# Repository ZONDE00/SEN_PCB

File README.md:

# SEN_PCB
Must be atleast 18 years old to clone

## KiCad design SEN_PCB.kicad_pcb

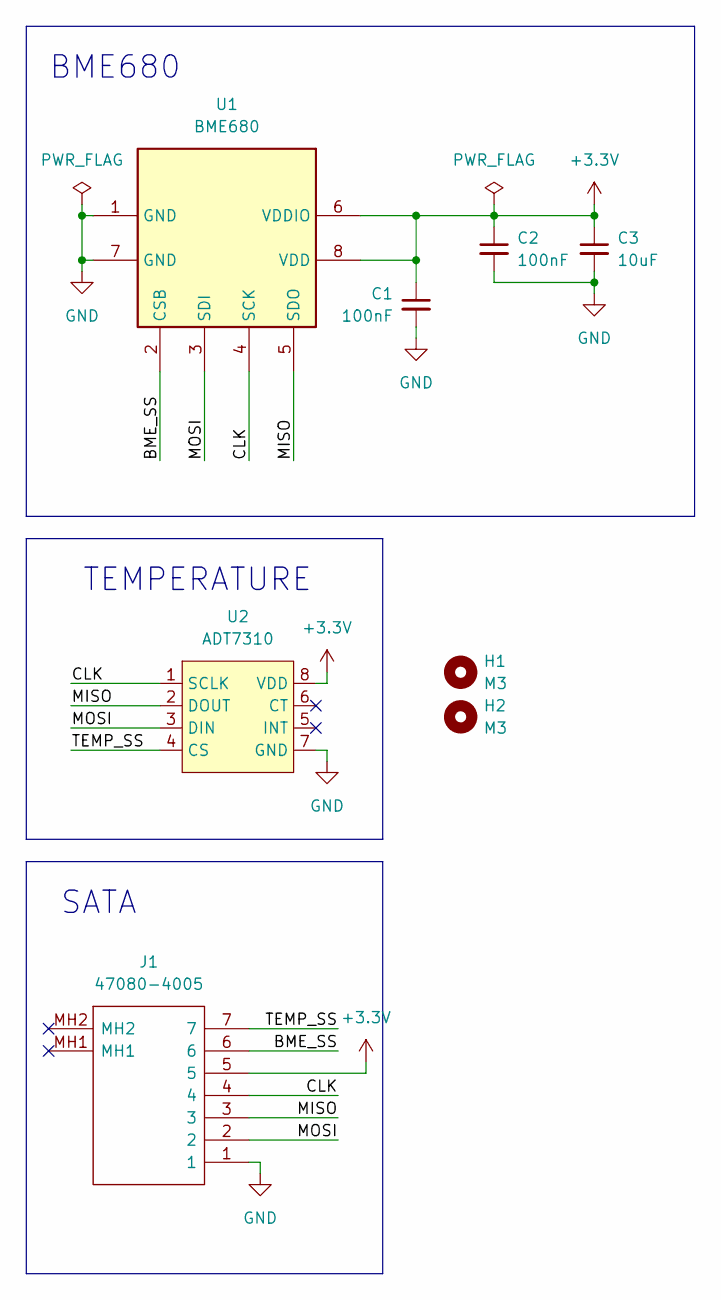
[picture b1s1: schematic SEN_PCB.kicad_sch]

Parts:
C1, C2: 100nF; C_0402_1005Metric
C3: 10uF; C_0805_2012Metric
H1, H2: M3; MountingHole_3.2mm_M3
J1: 47080-4005; 470804005; Mouser Part Number 538-47080-4005
U1: BME680; Bosch_LGA-8_3x3mm_P0.8mm_ClockwisePinNumbering
U2: ADT7310; SOIC-8_3.9x4.9mm_P1.27mm

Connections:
+3.3V: C1.1, C2.1, C3.1, J1.5, U1.6 (VDDIO), U1.8 (VDD), U2.8 (VDD)
/BME_SS: J1.6, U1.2 (CSB)
/CLK: J1.4, U1.4 (SCK), U2.1 (SCLK)
/MISO: J1.3, U1.5 (SDO), U2.2 (DOUT)
/MOSI: J1.2, U1.3 (SDI), U2.3 (DIN)
/TEMP_SS: J1.7, U2.4 (CS)
GND: C1.2, C2.2, C3.2, J1.1, U1.1 (GND), U1.7 (GND), U2.7 (GND)

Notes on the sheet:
SATA
TEMPERATURE
BME680

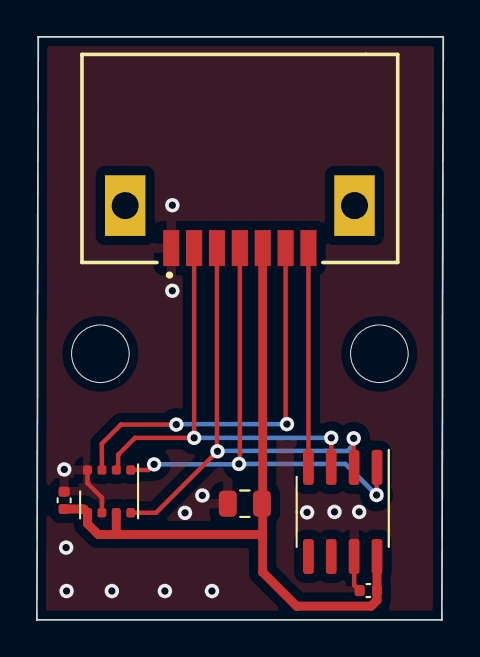
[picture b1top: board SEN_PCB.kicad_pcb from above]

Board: 2 copper layers, 22.6 x 32.4 mm, 8 parts (0 on the bottom side), 7 nets.

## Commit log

2022-09-25 Init
2022-12-13 1V KiCad
    Changed form-factor to more appropriate one.
    Changed connector pinout meaning to match new pinout on MCU board.
